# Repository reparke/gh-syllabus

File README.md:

[University of Southern California](https://www.usc.edu)

[Viterbi School of Engineering](https://viterbischool.usc.edu/)

[Information Technology Program](https://itp.usc.edu/)

# ITP 348 – Introduction to Physical Computing
This course is offered by the [Information Technology Program](https://itp.usc.edu/) in the [Viterbi School of Engineering](https://viterbischool.usc.edu/) at the [University of Southern California](https://www.usc.edu)

The live course website can be found at **https://reparke.github.io/ITP348-Physical-Computing/**

For more information about how this course is built, check out the [process](how_this_site_is_built.md).

#### Credits

I sought to use only images that were my own, that were in the public domain, or that had Creative Commons licenses. If an image appears that isn't licensed properly, please let me know and I will take it down.

This work is licensed under a
[Attribution-NonCommmercial-ShareAlike 4.0 International](https://creativecommons.org/licenses/by-nc-sa/4.0/)

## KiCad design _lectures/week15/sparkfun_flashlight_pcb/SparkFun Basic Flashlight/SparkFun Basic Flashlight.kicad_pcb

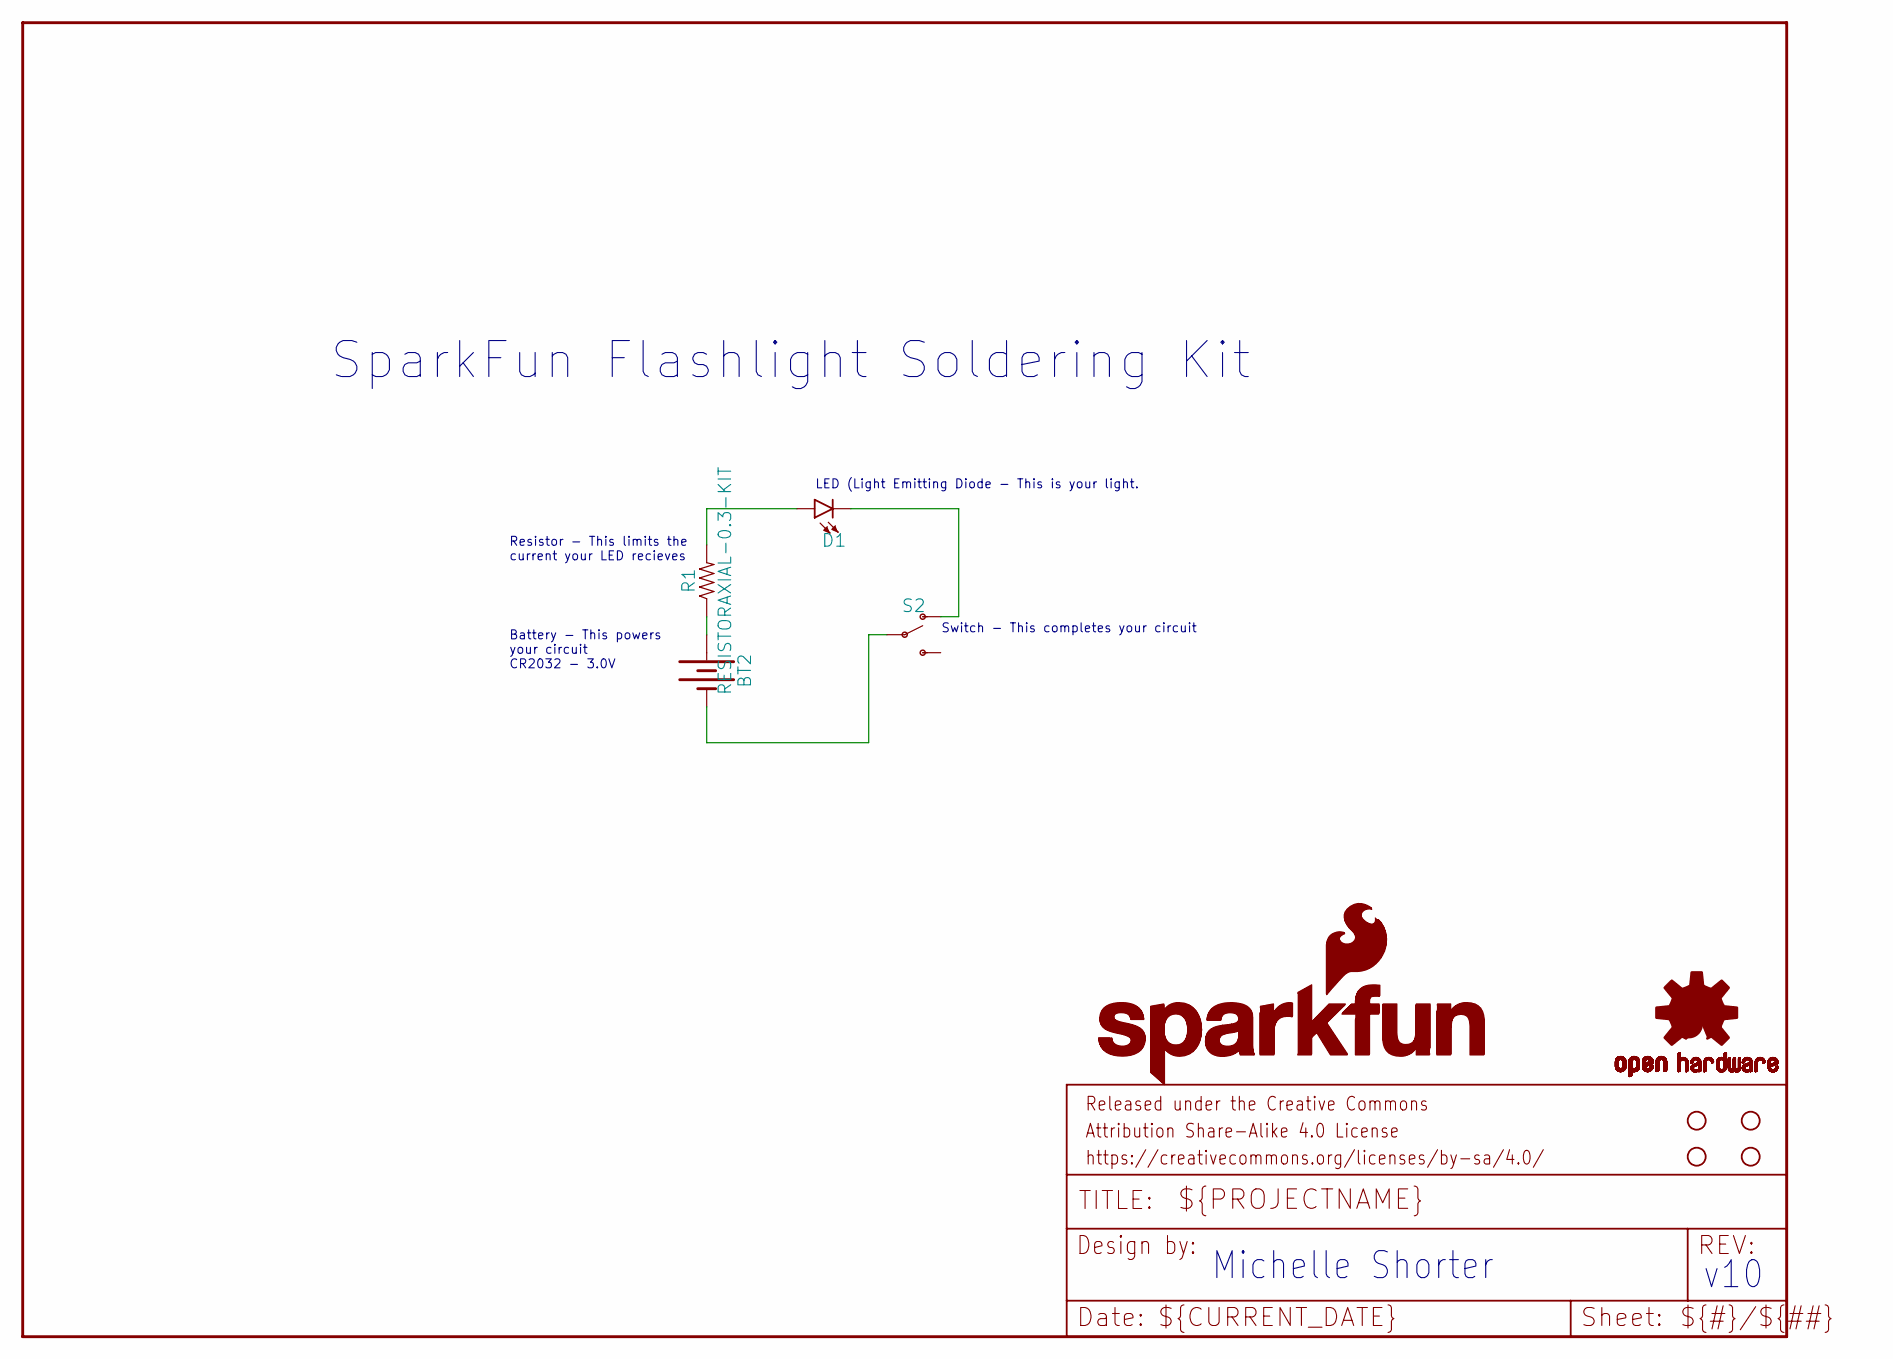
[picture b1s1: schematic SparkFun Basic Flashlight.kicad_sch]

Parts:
BT2: BATTERY-20MM_PTH_KIT; BATTCOM_20MM_PTH_KIT
D1: LED-5MM-KIT-NO-SILK; LED_5MM-KIT-NO-SILK
FRAME1: FRAME-LETTER; CREATIVE_COMMONS
H1, H2, H3, H4: STAND-OFF
LOGO1: OSHW-LOGOS; OSHW-LOGO-S
LOGO2: SFE_LOGO_FLAME.1_INCH; SFE_LOGO_FLAME_.1
LOGO3: SFE_LOGO_NAME_FLAME.2_INCH; SFE_LOGO_NAME_FLAME_.2
LOGO4: SFE_LOGO_NAME.2_INCH; SFE_LOGO_NAME_.2
R1: RESISTORAXIAL-0.3-KIT; AXIAL-0.3-KIT
S2: SWITCH-SPDT-PTH-11.6X4.0MM-KIT; SWITCH_SPDT_PTH_11.6X4.0MM_KIT

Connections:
ANODE: D1.K (C), S2.1 (O)
CATHODE: BT2.1 (+), R1.P$1 (1)
GND: D1.A, R1.P$2 (2)
unnamed: BT2.2 (-), S2.2

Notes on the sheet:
LED (Light Emitting Diode - This is your light.
Battery - This powers your circuit CR2032 - 3.0V
Michelle Shorter
SparkFun Flashlight Soldering Kit
v10
Resistor - This limits the current your LED recieves
Switch - This completes your circuit

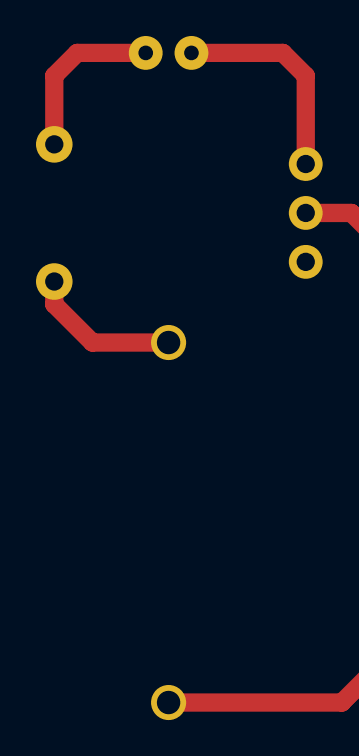
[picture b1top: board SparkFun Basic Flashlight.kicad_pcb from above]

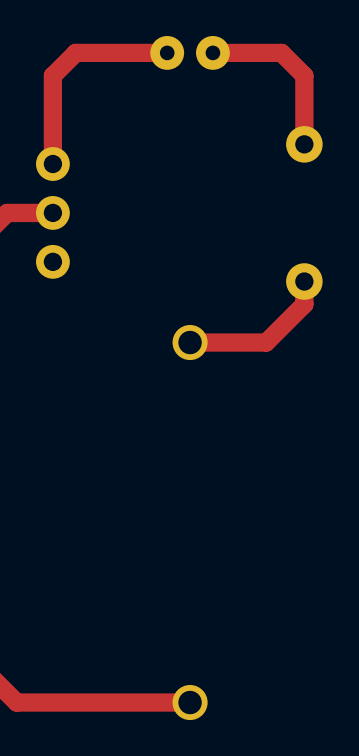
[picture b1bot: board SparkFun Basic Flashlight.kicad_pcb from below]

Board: 2 copper layers, 28 parts (7 on the bottom side), 4 nets.

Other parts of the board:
U$1: CR20325
U$2: FLASHLIGHT6
U$3: FOLD_LED_OVER0
U$4: BATTERY11
U$5: LET_YOUR11
U$6: LIGHT_SHINE12
U$7: LONG_LEG2
U$8: OFF4
U$9: ON3
U$10: SHORT_LEG1
U$11: SPARKFUN#COM#FLASHLIGHT13
U$12: LED12
U$13: THIS_FLASHLIGHT_BELONGS_TO#10
U$14: RESISTOR14
U$15: SWITCH13

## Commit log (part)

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2021-01-14 finalized Spring 2021 schedule
2021-01-14 added social issues assignment
2021-01-23 added wk 3 reading
2021-02-04 wk 3 updates
2021-02-07 wk 4 updates
2021-02-15 wk 5 updates
2021-02-21 wk 6 updates
2021-02-24 a5 picture
2021-02-27 wk 7 updates
2021-02-28 w7 update
2021-03-01 wk 7 and move DHT11 notes
2021-03-01 new a7
2021-03-02 revised week 7 state machines
2021-03-03 updated stoplight wk7
2021-03-07 updated blynk a9
2021-03-09 updated wk8
2021-03-13 updated wk9
2021-03-22 adjust wk 13-14
2021-03-23 adjust json wk11
2021-04-01 adjust wk 10
2021-04-06 adjust wk 12
2021-04-08 fixed heart rate reading by adding millis delay on oled redraw
2021-04-12 week 13
2021-05-14 final changes of spring 2021
2021-05-14 changed course title
2021-07-24 getting ready for fall 2021
2021-08-17 start of fall 2021 updates
2021-08-19 changed piazza link
2021-08-24 week 1
2021-08-29 update assignment 1
2021-08-30 update assignment 3
2021-08-30 update assignment 4
2021-08-31 update assignments submission details
2021-09-03 update week 2
2021-09-06 blynkair
2021-09-07 changed title
2021-09-07 changed name
2021-09-07 a4 update
2021-09-09 update week 3
2021-09-10 navigation and a5-6
2021-09-11 social issues
2021-09-11 assignment formatting revisions
2021-09-16 assignment due date revisions
2021-09-20 die assignment
2021-09-22 week 5
2021-09-23 oled
2021-09-24 oled i2c
2021-09-24 oled with i2c
2021-09-25 update for Qwiic OLED + MAX30101; removed timers
2021-09-25 cleaned and finalized SPI OLED + MAX30101
2021-09-25 archived old and partially working versions
2021-09-25 modified for Qwiic OLED
2021-09-25 reorganized files; remove redundant images
2021-09-25 archived old versions
2021-09-26 update for Qwiic OLED
2021-09-27 corrected rgb cathode
2021-09-28 blynk lectures and exercise updates
2021-09-29 blynk lectures and exercise updates; before adding quick reference
2021-09-30 add reference section
2021-09-30 updated reference section
2021-10-01 wk6 and 7
2021-10-01 week 7
2021-10-01 added oled to stoplight
2021-10-03 revising state machines
2021-10-04 tea brewer state machine
2021-10-04 new tea brewer A9 assignment
2021-10-05 new tea brewer A9 solution
2021-10-06 stoplight in class
2021-10-06 update washing machine state machine
2021-10-08 washing machine state machine + week 8 reading
2021-10-09 assignment 7 updates
2021-10-13 week 8 speaker and dc motor
2021-10-13 bt car build date change
2021-10-18 week 8 motors lecture
2021-10-18 updating reference section
2021-10-20 week 9 updates
2021-10-26 week 10 updates
2021-10-26 project updates
2021-11-02 wk 10
2021-11-02 wk11
2021-11-03 wk 11
2021-11-09 wk 12
2021-11-17 wk 13 RFID
2021-11-18 wk 13 accel
2021-12-01 wk 15
2021-12-09 final fall 2021
2021-12-22 spring revisions
2021-12-22 accounts for spring break in date calculation
2021-12-22 prepping for Spring 2022
2022-01-19 wk 1 updates
2022-01-26 wk 2 updates and captive wifi
2022-01-26 captive wifi
2022-02-06 Changing A5 to button timer
2022-02-06 week 4
2022-02-06 a5 update
2022-02-11 a5 update and week 5
2022-02-12 reference and project updates
2022-02-13 reference section updates
2022-03-10 moved bt car starting project
2022-03-11 update a9
2022-04-14 added weatherstack API + JSON
2022-04-21 Using new ARGON-RFID-MFRC522 library
2022-04-21 adding sleep lecture notes
2022-04-21 more update to sleep lecture
2022-05-03 end updates for Spring 2022
2022-05-03 changing branch name
2022-08-05 start of fall 2022
2022-09-14 weeks 1-3
2022-09-26 update week 6
2022-10-05 updates for DHT 20
2022-10-08 replace accel with adxl345
2022-10-12 updated A8 Blynk to v3
2022-10-13 updated a9 car to new chassis
2022-10-19 updated bluetooth notes and exercises
2022-10-21 update a8
2022-10-24 swapped exercises for weeks 10 and 11
2022-10-24 wk 10 and bluetooth car
2022-10-31 updating ultra sonic exercises
2022-11-02 updated code for pulse sensor watch
2022-11-09 updated week 12
2022-11-16 week 13 and update accel
2022-12-07 end of Fall 2022 updates
2023-01-04 start of Spring 2023 updates
2023-01-23 week 3 notes
2023-01-25 week 3 exercises
2023-01-25 moving old exercises to _archive subfolders
2023-02-15 update through week 6
2023-02-22 update through week 7
2023-02-27 update through week 8
2023-03-06 update through week 9
2023-03-08 add accessiblity for resistor reading and color blindness
2023-03-20 week 10 udpates
2023-03-27 week 11 updates
2023-05-16 final updates for Spring 2023
2023-07-19 first update Fall 2023; adding dates
2023-08-08 updated breadboard notes
2023-08-23 reorganize pre lecture videos
2023-08-23 week 1 changes
2023-08-25 adding old particle app instructions
2023-08-27 updated kit
2023-08-30 week 2 updates
2023-09-10 week3 updates
2023-09-12 week 4 updates
2023-09-12 week4 updates
2023-09-20 week5 updates
2023-09-27 week6 updates
2023-10-02 week7 updates
2023-10-11 week 8 before changing JSON process
2023-10-13 week8 updates
2023-11-08 week 12 updates
2023-11-13 week 13 updates
2023-11-20 week 14 updates
2023-11-28 week 15 updates
2023-12-17 end of fall 2023 updates
2024-01-03 early spring 2024 updates
2024-01-05 spring 2024 calendar corrections
2024-01-06 added particle troubleshooting
2024-01-10 week 1 updates
2024-01-13 adding instructions for device doctor
2024-01-30 through week 3 updates
2024-01-31 week 4 update
2024-02-09 part of week 5
2024-02-13 week 6 update + Blynk changes
2024-03-06 week 9
2024-03-19 correcting download starting code URL
2024-04-03 weeks 10-12
2024-04-05 Create itp_heartrate_notes
2024-04-06 updated watch and 5v step-up regulator
2024-05-18 final changes to spring 2024
2024-05-20 updated assignment 0
2024-05-21 updates to weeks1-2
2024-05-23 changes before working on bluetooth car
2024-05-29 some changes to week 5
2024-05-29 smart watch updates
2024-06-02 completed week 4 lectures
2024-06-03 finished week 5 and 6 lectures and excercises, and weeks 4,5,6 readings
2024-06-03 edited one photo week 4 lecture
2024-06-04 checked weeks 4-6 vscode filed and updated where necessary
2024-06-05 smart watch and project updates
2024-06-05 updating typos in wk6
2024-06-19 finished lectures and exercises for weeks 7-8
2024-06-21 finished all lectures and exercises for weeks 9-10 and some of 11
2024-06-29 completed all remaining lectures and exercises, except Week X and heart rate related
2024-07-01 fixed some photos in lecture 11
2024-07-02 reuploading a previously failed change
2024-07-03 all readings, some reference done
2024-07-06 finished all reference, only some incomplete to be discussed later
2024-07-07 finished all assignment pages, fixed other errors
2024-07-07 fixed other errors
2024-07-07 more errors
2024-07-09 edits made during meeting
2024-07-27 fixed previous errors to maintain consistency. updated some photos.
2024-07-30 finished all week x lectures
2024-07-30 completed week X exercises
2024-08-17 updating fall schedule
2024-08-18 updated schedule for fall
2024-08-18 corrected typo in project
2024-08-23 updated workbench video
2024-08-28 updated week 1
2024-09-05 updated week 2
2024-09-09 updated week 3
2024-09-18 updated week 4
2024-09-25 updated week 5
2024-10-07 updated week 7
2024-10-16 updated week 8
2024-10-23 updated week 9
2024-10-28 updated week 10
2024-11-19 updated week 12 watch code
2025-01-04 last commit of Fall 2024
2025-01-05 adjusted schedule for Spring 2025
2025-01-07 updated Piazza link
2025-01-13 start week 1

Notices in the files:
README.md:
License: CC BY-NC-SA 4.0
_lectures/week15/sparkfun_flashlight_pcb/SparkFun Basic Flashlight/SparkFun Basic Flashlight.kicad_sch:
https://creativecommons.org/licenses/by-sa/4.0
Released under the Creative Commons
